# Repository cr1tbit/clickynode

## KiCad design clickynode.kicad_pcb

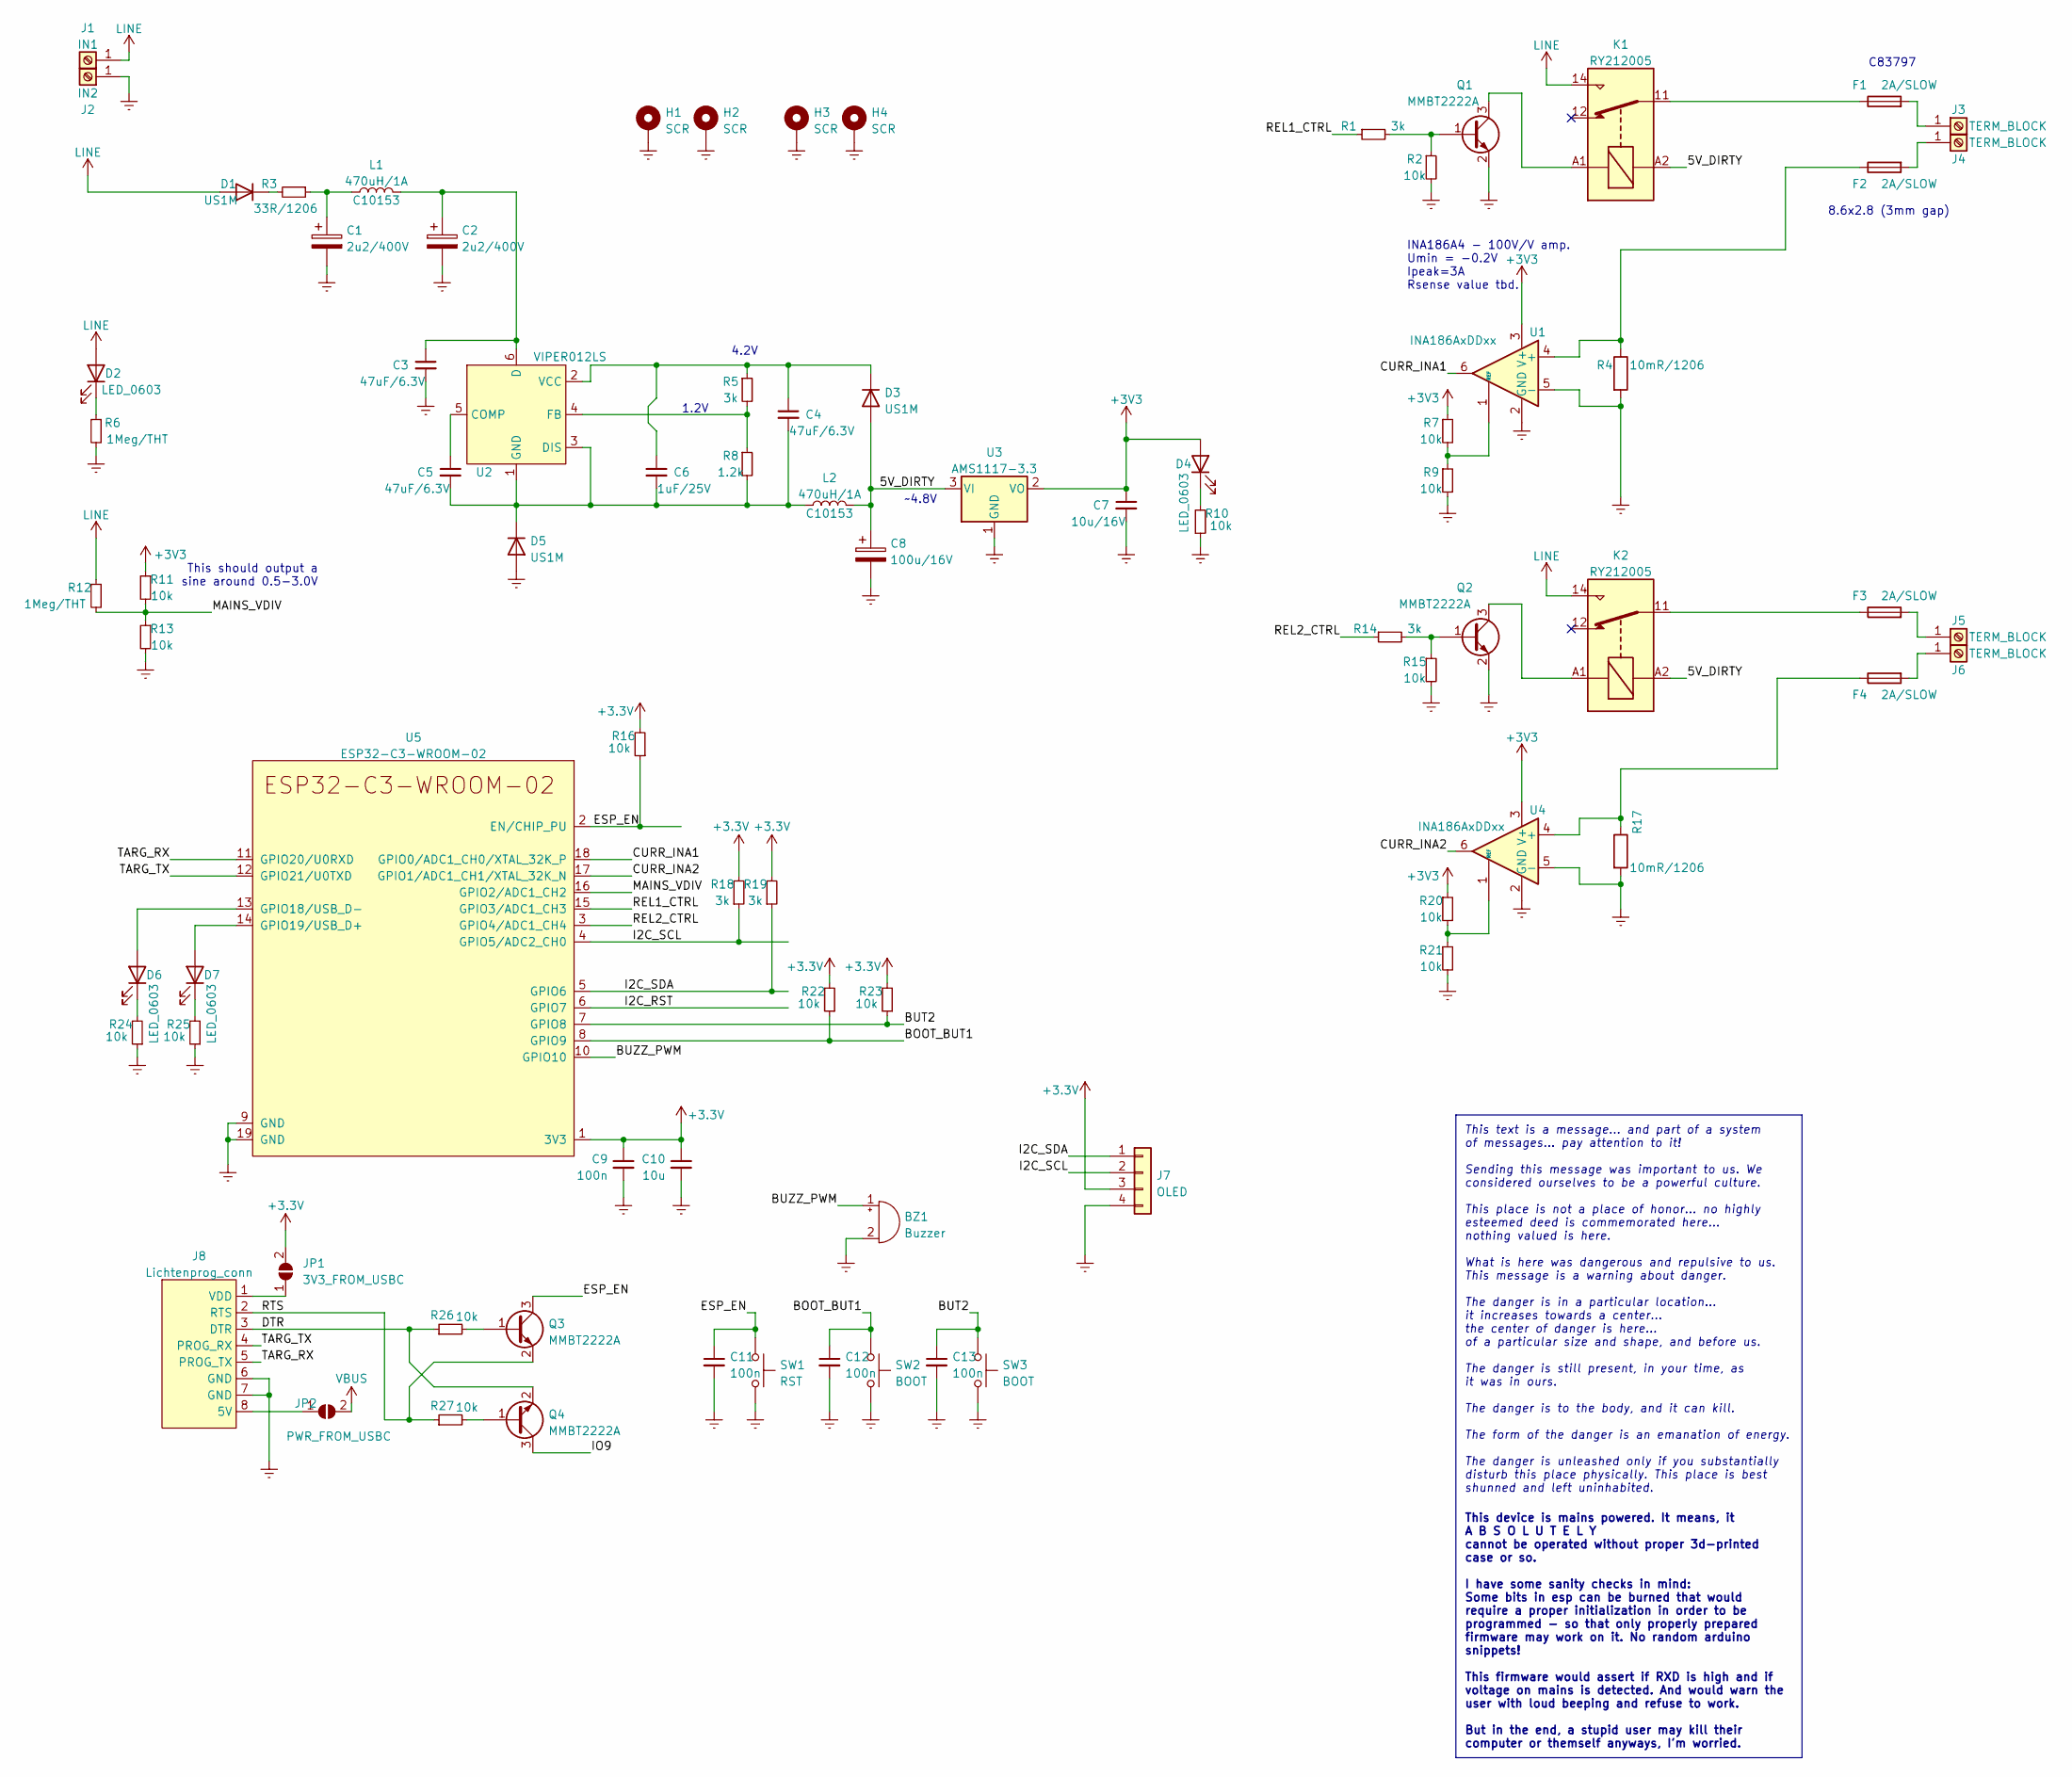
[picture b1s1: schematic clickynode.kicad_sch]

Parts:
BZ1: Buzzer; Buzzer_12x9.5RM7.6
C1, C2: 2u2/400V; CP_Radial_D8.0mm_P3.80mm
C3, C4, C5: 47uF/6.3V; C_1206_3216Metric; LCSC C19702
C6: 1uF/25V; C_1206_3216Metric; LCSC C19702
C7: 10u/16V; C_1206_3216Metric; LCSC C19702
C8: 100u/16V; CP_Radial_D8.0mm_P3.80mm
C9, C11, C12, C13: 100n; C_0402_1005Metric
C10: 10u; C_0603_1608Metric
D1, D3, D5: US1M; D_SMA
D2, D4, D6, D7: LED_0603; LED_0603_1608Metric_Pad1.05x0.95mm_HandSolder
F1, F2, F3, F4: 2A/SLOW; Fuseholder_Littelfuse_Nano2_154x
H1, H2, H3, H4: SCR; MountingHole_3.2mm_M3_Pad_TopOnly
J1: IN1; DG235-5.0
J2: IN2; DG235-5.0
J3, J4, J5, J6: TERM_BLOCK; DG235-5.0
J7: OLED; PinHeader_1x04_P2.54mm_Vertical
J8: Lichtenprog_conn; Lichtenprog
JP1: 3V3_FROM_USBC; SolderJumper-2_P1.3mm_Open_TrianglePad1.0x1.5mm
JP2: PWR_FROM_USBC; SolderJumper-2_P1.3mm_Open_TrianglePad1.0x1.5mm
K1, K2: RY212005; Relay_1-Form-C_Schrack-RYII_RM3.2mm
L1, L2: 470uH/1A; L_Pulse_PA4320; JLC C10153
Q1, Q2, Q3, Q4: MMBT2222A; SOT-23
R1, R5, R14, R18, R19: 3k; R_0402_1005Metric
R2, R7, R9, R11, R13, R15, R20, R21: 10k; R_0402_1005Metric
R3: 33R/1206; R_1206_3216Metric
R4, R17: 10mR/1206; R_1206_3216Metric_Pad1.30x1.75mm_HandSolder
R6, R12: 1Meg/THT; R_0402_1005Metric
R8: 1.2k; R_0402_1005Metric
R10, R16, R22, R23, R24, R25, R26, R27: 10k; R_0402_1005Metric; LCSC C25117
SW1: RST; SW_PUSH_6mm_H4.3mm
SW2, SW3: BOOT; SW_PUSH_6mm_H4.3mm
U1, U4: INA186AxDDxx; Texas_R-PDSO-G6
U2: VIPER012LS; SSOP-10_3.9x4.9mm_P1.00mm
U3: AMS1117-3.3; SOT-223-3_TabPin2
U5: ESP32-C3-WROOM-02

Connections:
+3.3V: C9.1, C10.1, J7.3, JP1.2 (B), R16.2, R18.2, R19.2, R22.2, R23.2, U5.1 (3V3)
+3V3: C7.1, D4.2 (A), R7.1, R11.1, R20.1, U1.3 (V+), U3.2 (VO), U4.3 (V+)
/5V_DIRTY: C8.1, D3.2 (A), K1.A2, K2.A2, L2.2, U3.3 (VI)
/BOOT_BUT1: C12.1, R22.1, SW2.1, U5.8 (GPIO9)
/BUT2: C13.1, R23.1, SW3.1, U5.7 (GPIO8)
/BUZZ_PWM: BZ1.1 (-), U5.10 (GPIO10)
/CURR_INA1: U1.6, U5.18 (GPIO0/ADC1_CH0/XTAL_32K_P)
/CURR_INA2: U4.6, U5.17 (GPIO1/ADC1_CH1/XTAL_32K_N)
/DTR: J8.3 (DTR), Q4.2 (E), R26.1
/ESP_EN: C11.1, Q3.3 (C), R16.1, SW1.1, U5.2 (EN/CHIP_PU)
/I2C_RST: U5.6 (GPIO7)
/I2C_SCL: J7.2, R18.1, U5.4 (GPIO5/ADC2_CH0)
/I2C_SDA: J7.1, R19.1, U5.5 (GPIO6)
/IO9: Q4.3 (C)
/MAINS_VDIV: R11.2, R12.2, R13.1, U5.16 (GPIO2/ADC1_CH2)
/REL1_CTRL: R1.1, U5.15 (GPIO3/ADC1_CH3)
/REL2_CTRL: R14.1, U5.3 (GPIO4/ADC1_CH4)
/RTS: J8.2 (RTS), Q3.2 (E), R27.1
/TARG_RX: J8.5 (PROG_TX), U5.11 (GPIO20/U0RXD)
/TARG_TX: J8.4 (PROG_RX), U5.12 (GPIO21/U0TXD)
D: C2.1, C3.1, L1.2, U2.6 (D), U2.7 (D), U2.8 (D), U2.9 (D), U2.10 (D)
Earth: BZ1.2 (+), C1.2, C2.2, C3.2, C7.2, C8.2, C9.2, C10.2, C11.2, C12.2, C13.2, D5.2 (A), H1.1, H2.1, H3.1, H4.1, J2.1, J7.4, J8.6 (GND), J8.7 (GND), Q1.2 (E), Q2.2 (E), R2.2, R4.2, R6.2, R9.2, R10.1, R13.2, R15.2, R17.2, R21.2, R24.1, R25.1, SW1.2, SW2.2, SW3.2, U1.2 (GND), U1.5 (-), U3.1 (GND), U4.2 (GND), U4.5 (-), U5.9 (GND), U5.19 (GND)
LINE: D1.2 (A), D2.2 (A), J1.1, K1.14, K2.14, R12.1
unnamed: C1.1, L1.1, R3.1
unnamed: C4.1, C6.1, D3.1 (K), R5.1, U2.2 (VCC)
unnamed: C4.2, C5.2, C6.2, D5.1 (K), L2.1, R8.2, U2.1 (GND), U2.3 (DIS)
unnamed: C5.1, U2.5 (COMP)
unnamed: D1.1 (K), R3.2
unnamed: D2.1 (K), R6.1
unnamed: D4.1 (K), R10.2
unnamed: D6.1 (K), R24.2
unnamed: D6.2 (A), U5.13 (GPIO18/USB_D-)
unnamed: D7.1 (K), R25.2
unnamed: D7.2 (A), U5.14 (GPIO19/USB_D+)
unnamed: F1.1, K1.11
unnamed: F1.2, J3.1
unnamed: F2.1, R4.1, U1.4 (+)
unnamed: F2.2, J4.1
unnamed: F3.1, K2.11
unnamed: F3.2, J5.1
unnamed: F4.1, R17.1, U4.4 (+)
unnamed: F4.2, J6.1
unnamed: J8.1 (VDD), JP1.1 (A)
unnamed: J8.8 (5V), JP2.1 (A)
unnamed: K1.A1, Q1.3 (C)
unnamed: K2.A1, Q2.3 (C)
unnamed: Q1.1 (B), R1.2, R2.1
unnamed: Q2.1 (B), R14.2, R15.1
unnamed: Q3.1 (B), R26.2
unnamed: Q4.1 (B), R27.2
unnamed: R5.2, R8.1, U2.4 (FB)
unnamed: R7.2, R9.1, U1.1 (REF)
unnamed: R20.2, R21.1, U4.1 (REF)
VBUS: JP2.2 (B)

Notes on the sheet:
C83797
8.6x2.8 (3mm gap)
4.2V
This text is a message... and part of a system of messages... pay attention to it! Sending this message was important to us. We considered ourselves to be a powerful culture. This place is not a place of honor... no highly esteemed deed is commemorated here... nothing valued is here. What is here w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
~4.8V
1.2V
This device is mains powered. It means, it A B S O L U T E L Y cannot be operated without proper 3d-printed case or so. I have some sanity checks in mind: Some bits in esp can be burned that would require a proper initialization in order to be programmed - so that only properly prepared firmware ma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
This should output a sine around 0.5-3.0V
INA186A4 - 100V/V amp. Umin = -0.2V Ipeak=3A Rsense value tbd.

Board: 2 copper layers, 82 parts (2 on the bottom side), 51 nets, no tracks yet.

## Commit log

2023-01-29 repoify the project
